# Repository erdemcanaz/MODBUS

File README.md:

# LoRa_Modbus
The goal of this project is to design a hardware implementation that enables wireless Modbus communication using the LoRa protocol.

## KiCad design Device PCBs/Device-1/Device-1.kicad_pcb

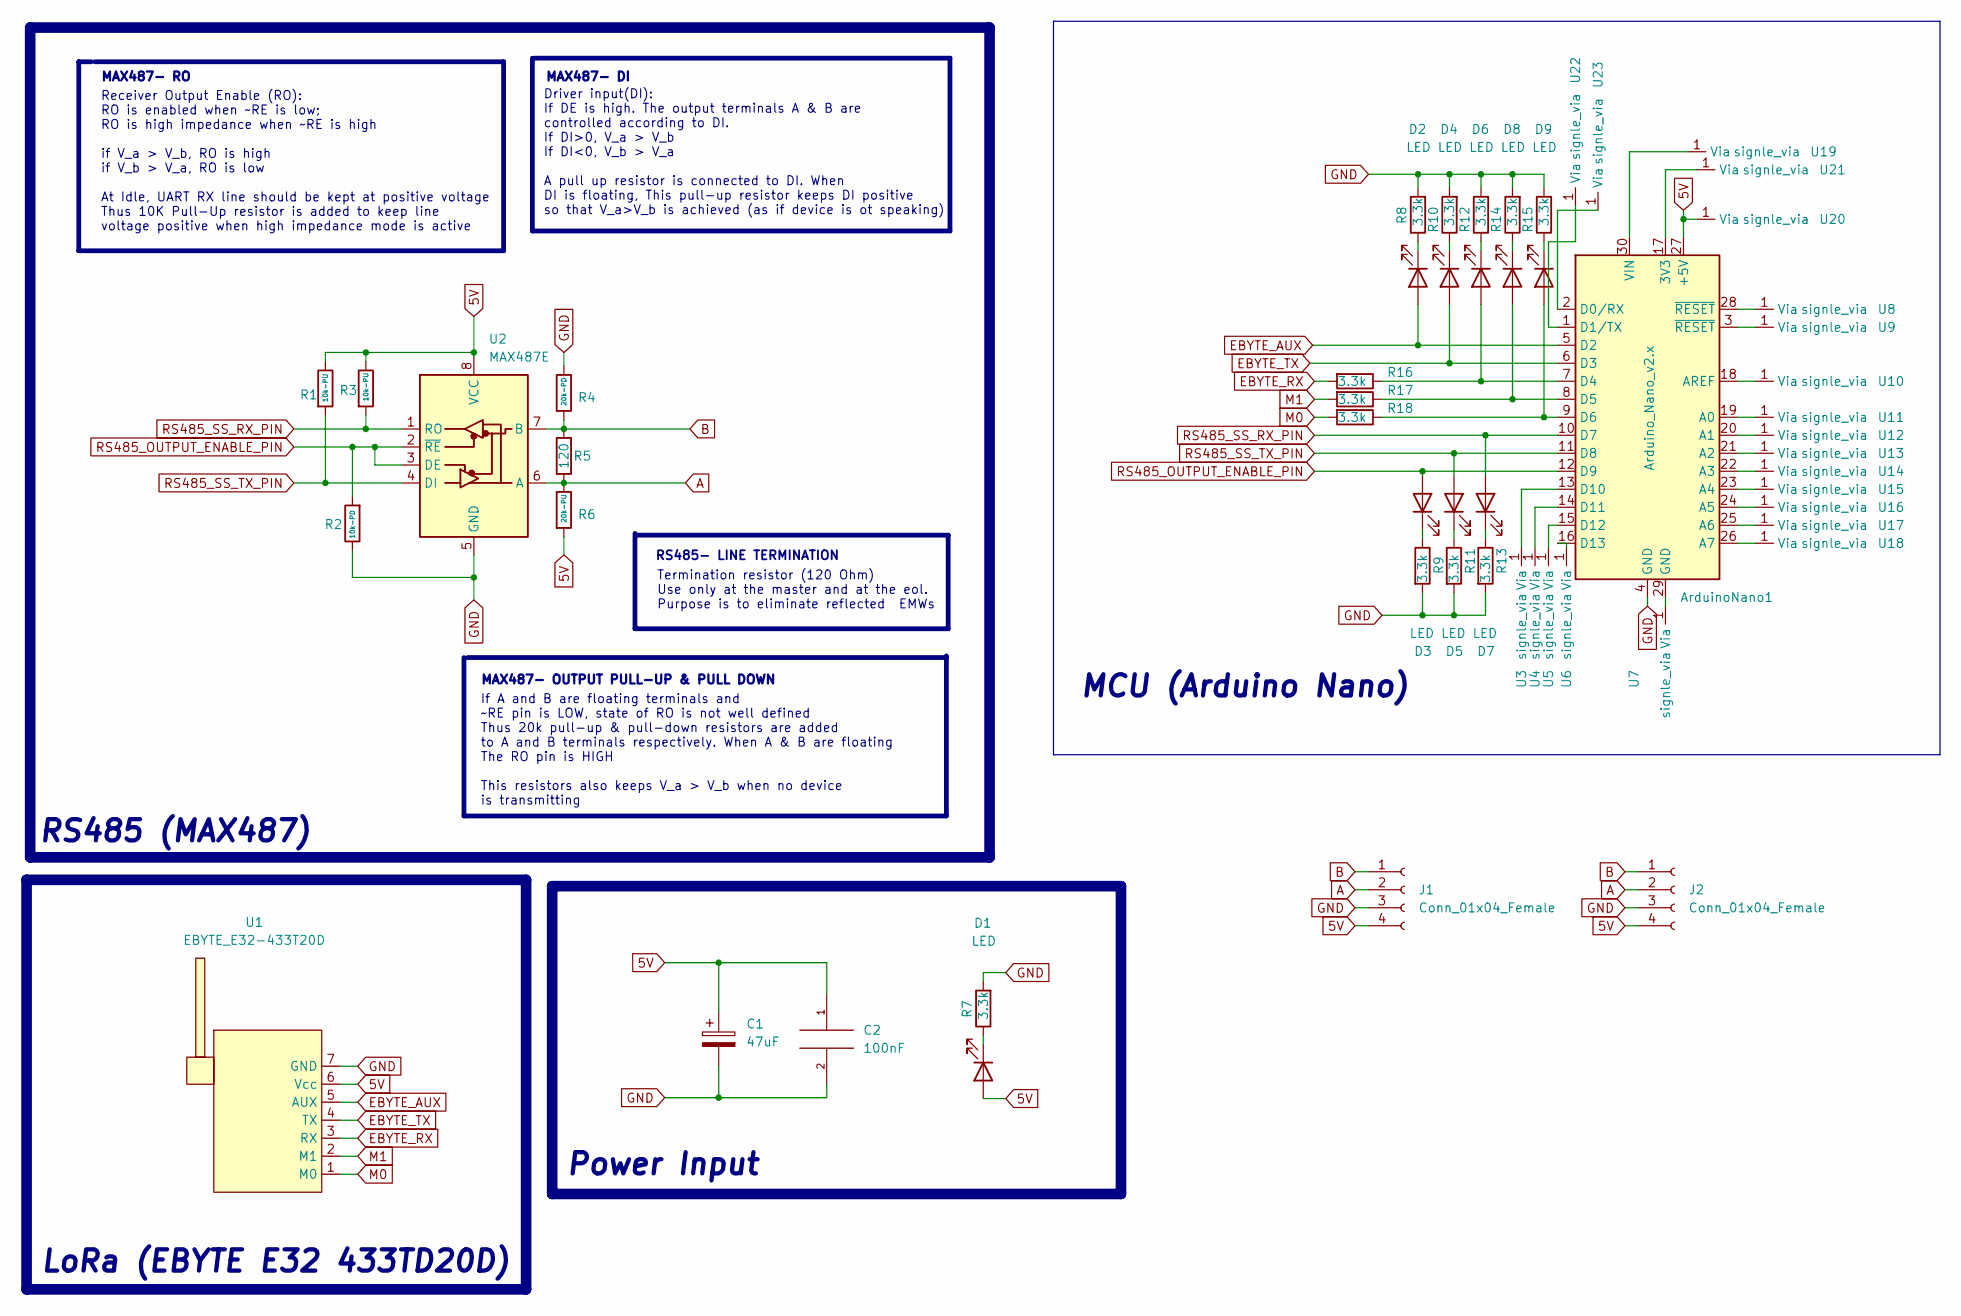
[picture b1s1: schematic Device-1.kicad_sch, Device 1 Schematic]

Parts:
ArduinoNano1: Arduino_Nano_v2.x; Arduino_Nano
C1: 47uF; CP_Elec_6.3x5.2
C2: 100nF; C_1206_3216Metric
D1, D2, D3, D8, D9: LED; lm281B-3000K
D4, D5, D6, D7: LED; lm281B-6500K
J1: Conn_01x04_Female; PinSocket_1x04_P2.54mm_Vertical
J2: Conn_01x04_Female; output_vias
R1, R3: 10k-PU; R_1206_3216Metric
R2: 10k-PD; R_1206_3216Metric
R4: 20k-PD; R_1206_3216Metric
R5: 120; R_1206_3216Metric
R6: 20k-PU; R_1206_3216Metric
R7, R8, R9, R10, R11, R12, R13, R14, R15, R16, R17, R18: 3.3k; R_1206_3216Metric
U1: EBYTE_E32-433T20D; EBYTE-E32-433T20D
U2: MAX487E; DIP-8_W7.62mm
U3, U4, U5, U6, U7, U8, U9, U10, U11, U12, U13, U14, U15, U16, U17, U18, U19, U20, U21, U22, U23: signle_via; single_via

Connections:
5V: ArduinoNano1.27 (+5V), C1.1, C2.1, D1.2 (A), J1.4, J2.4, R1.1, R3.1, R6.2, U1.6 (Vcc), U2.8 (VCC), U20.1 (Via)
A: J1.2, J2.2, R5.2, R6.1, U2.6 (A)
B: J1.1, J2.1, R4.2, R5.1, U2.7 (B)
EBYTE_AUX: ArduinoNano1.5 (D2), D2.2 (A), U1.5 (AUX)
EBYTE_RX: R16.2, U1.3 (RX)
EBYTE_TX: ArduinoNano1.6 (D3), D4.2 (A), U1.4 (TX)
GND: ArduinoNano1.4 (GND), C1.2, C2.2, J1.3, J2.3, R2.1, R4.1, R7.2, R8.2, R9.2, R10.2, R11.2, R12.2, R13.2, R14.2, R15.2, U1.7 (GND), U2.5 (GND)
M0: R18.2, U1.1 (M0)
M1: R17.2, U1.2 (M1)
unnamed: ArduinoNano1.1 (D1/TX), U22.1 (Via)
unnamed: ArduinoNano1.2 (D0/RX), U23.1 (Via)
unnamed: ArduinoNano1.3 (~RESET), U9.1 (Via)
unnamed: ArduinoNano1.7 (D4), D6.2 (A), R16.1
unnamed: ArduinoNano1.8 (D5), D8.2 (A), R17.1
unnamed: ArduinoNano1.9 (D6), D9.2 (A), R18.1
unnamed: ArduinoNano1.13 (D10), U3.1 (Via)
unnamed: ArduinoNano1.14 (D11), U4.1 (Via)
unnamed: ArduinoNano1.15 (D12), U5.1 (Via)
unnamed: ArduinoNano1.16 (D13), U6.1 (Via)
unnamed: ArduinoNano1.17 (3V3), U21.1 (Via)
unnamed: ArduinoNano1.18 (AREF), U10.1 (Via)
unnamed: ArduinoNano1.19 (A0), U11.1 (Via)
unnamed: ArduinoNano1.20 (A1), U12.1 (Via)
unnamed: ArduinoNano1.21 (A2), U13.1 (Via)
unnamed: ArduinoNano1.22 (A3), U14.1 (Via)
unnamed: ArduinoNano1.23 (A4), U15.1 (Via)
unnamed: ArduinoNano1.24 (A5), U16.1 (Via)
unnamed: ArduinoNano1.25 (A6), U17.1 (Via)
unnamed: ArduinoNano1.26 (A7), U18.1 (Via)
unnamed: ArduinoNano1.28 (~RESET), U8.1 (Via)
unnamed: ArduinoNano1.29 (GND), U7.1 (Via)
unnamed: ArduinoNano1.30 (VIN), U19.1 (Via)
unnamed: D1.1 (K), R7.1
unnamed: D2.1 (K), R8.1
unnamed: D3.1 (K), R9.1
unnamed: D4.1 (K), R10.1
unnamed: D5.1 (K), R11.1
unnamed: D6.1 (K), R12.1
unnamed: D7.1 (K), R13.1
unnamed: D8.1 (K), R14.1
unnamed: D9.1 (K), R15.1
RS485_OUTPUT_ENABLE_PIN: ArduinoNano1.12 (D9), D3.2 (A), R2.2, U2.2 (~RE), U2.3 (DE)
RS485_SS_RX_PIN: ArduinoNano1.10 (D7), D7.2 (A), R3.2, U2.1 (RO)
RS485_SS_TX_PIN: ArduinoNano1.11 (D8), D5.2 (A), R1.2, U2.4 (DI)

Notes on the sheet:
MAX487- OUTPUT PULL-UP & PULL DOWN
RS485- LINE TERMINATION
RS485 (MAX487)
Driver input(DI): If DE is high. The output terminals A & B are controlled according to DI. If DI>0, V_a > V_b If DI<0, V_b > V_a A pull up resistor is connected to DI. When DI is floating, This pull-up resistor keeps DI positive so that V_a>V_b is achieved (as if device is ot speaking)
If A and B are floating terminals and ~RE pin is LOW, state of RO is not well defined Thus 20k pull-up & pull-down resistors are added to A and B terminals respectively. When A & B are floating The RO pin is HIGH This resistors also keeps V_a > V_b when no device is transmitting
MAX487- RO
MAX487- DI
Power Input
Receiver Output Enable (RO): RO is enabled when ~RE is low; RO is high impedance when ~RE is high if V_a > V_b, RO is high if V_b > V_a, RO is low At Idle, UART RX line should be kept at positive voltage Thus 10K Pull-Up resistor is added to keep line voltage positive when high impedance mode is ac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
Termination resistor (120 Ohm) Use only at the master and at the eol. Purpose is to eliminate reflected EMWs
LoRa (EBYTE E32 433TD20D)
MCU (Arduino Nano)

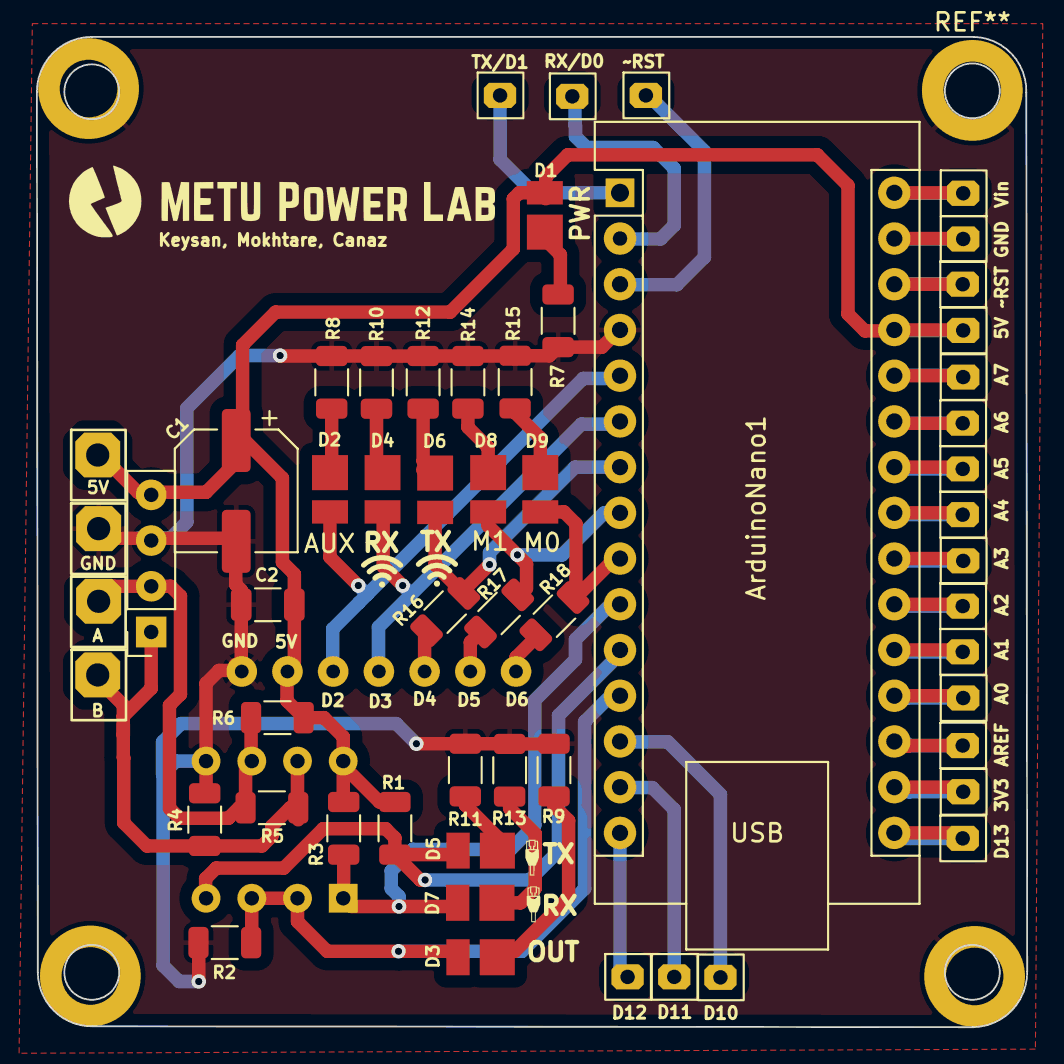
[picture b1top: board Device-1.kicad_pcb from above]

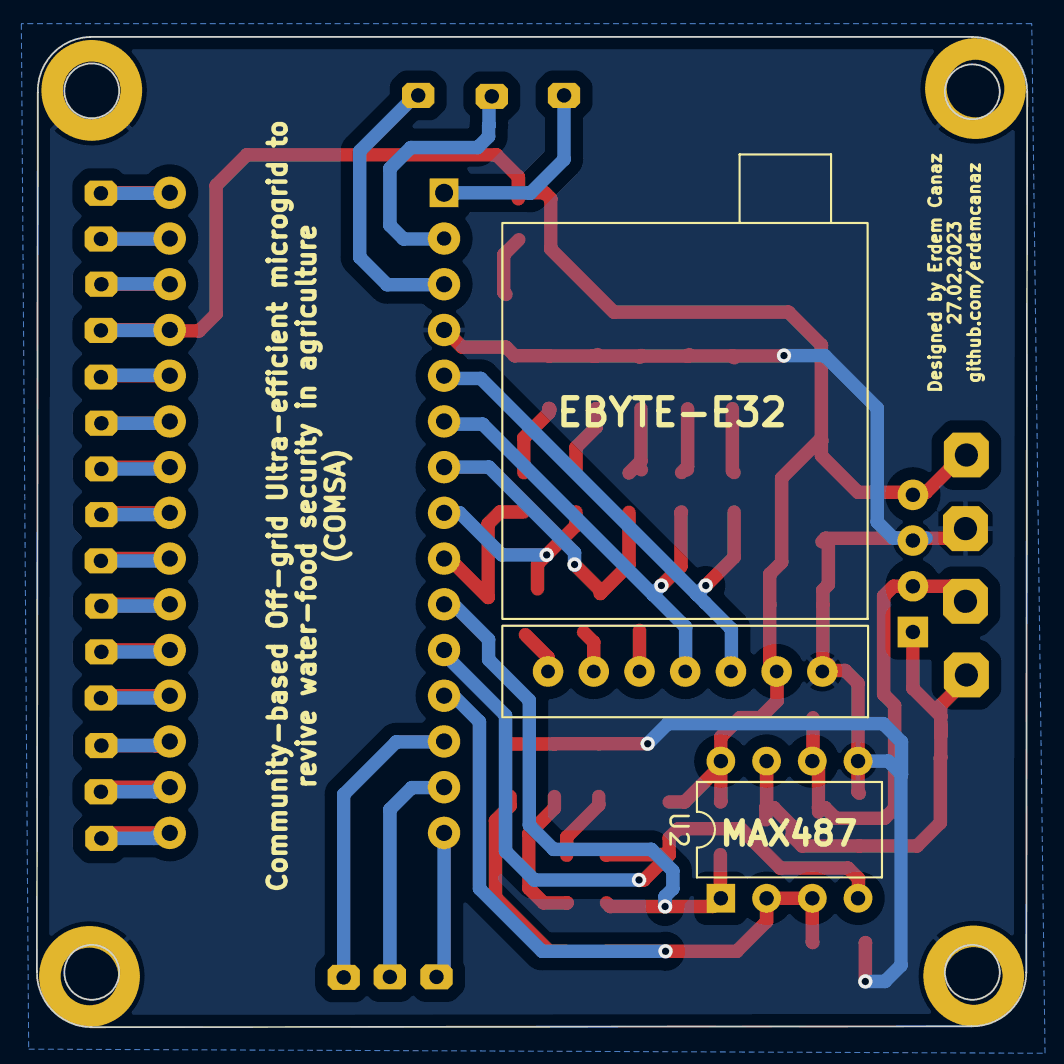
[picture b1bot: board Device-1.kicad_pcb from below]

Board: 2 copper layers, 55.0 x 55.0 mm, 55 parts (2 on the bottom side), 44 nets.

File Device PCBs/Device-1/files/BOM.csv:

Collated Components:,,,,,,,,,
Item,Qty,Reference(s),Value,Footprint,sipariþ adeti,,,,
1,1,ArduinoNano1,Arduino_Nano_v2.x,Module:Arduino_Nano,,,,,
2,1,C1,47uF,Capacitor_SMD:CP_Elec_6.3x5.2,12,,,,
3,1,C2,100nF,Capacitor_SMD:C_1206_3216Metric,20,,,,
4,5,"D1, D2, D3, D8, D9",LED,Device_1_project_footprints:lm281B-3000K,,,,,
5,4,"D4, D5, D6, D7",LED,Device_1_project_footprints:lm281B-6500K,,,,,
6,1,J1,Conn_01x04_Female,Connector_PinSocket_2.54mm:PinSocket_1x04_P2.54mm_Vertical,15,,,,
7,1,J2,Conn_01x04_Female,Device_1_project_footprints:output_vias,,,,,
8,2,"R1, R3",10k-PU,Resistor_SMD:R_1206_3216Metric,30,,,,
9,1,R2,10k-PD,Resistor_SMD:R_1206_3216Metric,15,,,,
10,1,R4,20k-PD,Resistor_SMD:R_1206_3216Metric,15,,,,
11,1,R5,120,Resistor_SMD:R_1206_3216Metric,30,,,,
12,1,R6,20k-PU,Resistor_SMD:R_1206_3216Metric,15,,,,
13,12,"R7, R8, R9, R10, R11, R12, R13, R14, R15, R16, R17, R18",3.3k,Resistor_SMD:R_1206_3216Metric,15,,,,
14,1,U1,EBYTE_E32-433T20D,Device_1_project_footprints:EBYTE-E32-433T20D,,,,,
15,1,U2,MAX487E,Package_DIP:DIP-8_W7.62mm,,,,,

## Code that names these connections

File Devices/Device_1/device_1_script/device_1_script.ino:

#include <SoftwareSerial.h>

//SOFTWARE RELATED STATIC VARIABLES
#define PACKAGE_SIZE_BYTE 44
#define HARDWARE_SERIAL_BAUD_RATE 9600
#define LORA_SOFTWARE_SERIAL_BAUD_RATE 9600
#define RS485_SOFTWARE_SERIAL_BAUD_RATE 9600

//HARDWARE RELATED STATIC VARIABLES
#define RS485_SOFTWARE_SERIAL_RX_PIN 7
#define RS485_SOFTWARE_SERIAL_TX_PIN 8
#define RS485_OUTPUT_ENABLE_PIN 9

#define EBYTE_M0_PIN 2
#define EBYTE_M1_PIN 3
#define EBYTE_TX_PIN 4  //Software serial RX
#define EBYTE_RX_PIN 5  //Software serial TX
#define EBYTE_AUX_PIN 6

#define DEVICE_CHANNEL 12  //0-255
#define DEVICE_ADDRESS 1 //0-65535
#define UART_PARITY_MODE 3 //3->8N1
#define UART_BAUD_MODE 3 //3-> 9600BPS
#define AIR_DATA_RATE_MODE 2 //2-> 2.4Kbps
#define FIXED_TRANSMISSION_MODE 1
#define IO_DRIVE_MODE 1 //1-> TX & AUX: push-pull, RX: pull-up
#define WIRELESS_WAKE_UP_MODE 0 //0-> 0.25kbps
#define FEC_MODE 1
#define POWER_MODE 0

//PARAMETRIC VARIABLES
#define DEBUG true
#define HARDWARE_SERIAL_WAIT_COMPUTER_TRANSFER_MS 10 
#define LORA_REQUEST_TIMEOUT_MS 750

//----------------------------------------------------------------------------
SoftwareSerial lora_serial_instance(EBYTE_TX_PIN, EBYTE_RX_PIN);  // software Rx, software Tx

void setup() {
  Serial.begin(HARDWARE_SERIAL_BAUD_RATE);
}

void loop() {
  listen_and_execute_valid_computer_orders();
}

uint16_t calculate_CRC(bool is_first_data, uint16_t previously_calculated_crc, uint16_t new_byte){ 
  uint16_t key = 40961; // 1010 0000 0000 0001
  if(is_first_data == true)previously_calculated_crc = 65535; //0xFFFF

  new_byte = new_byte ^ previously_calculated_crc;
  
  for (int i = 0; i < 8; i++)
  {
    bool should_XOR = false;
    if (new_byte % 2 == 1)
      should_XOR = true;
    new_byte = new_byte >> 1;
    if (should_XOR)
      new_byte = new_byte ^ key;
  }
  return new_byte;
}

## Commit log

2023-02-22 get_ebyte_parameters
    At this commit, the arduino is able to read the parameters of EBYTE-E32 series devices over software serial.
2023-02-22 device_1_master_is_finished
2023-02-22 set_ebyte_parameters
    In this commit, Arduino automatically overwrites the Ebyte E32 series device parameters. This is important because it allow us to use any device without preconfiguring. Just plug the lora device and 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
2023-02-24 Device 1 Slave and Master is finished
2023-02-24 Status code - Master is updated
2023-02-24 Status code - Slave is updated
2023-02-24 SerialMiddleware
2023-02-24 Python-Script SerialMiddleware is finished
2023-02-24 Python script is working well
2023-02-25 Arduino status codes
2023-02-25 Device-1 Schematic
2023-02-25 Device 1 PCB is finished
2023-02-27 slave config.h and tescom_SDDPV2200M
2023-03-01 PCB and slave fix
2023-03-01 PCBway gerbers are finished.
2023-03-10 Everything works
    1) PCB is finished (use larges holes for LoRa)
    2) Master and slave codes are finished
2023-03-24 Growat inverter is added as a device
2023-04-03 Machine labratory integration is started
2023-04-03 checkpoint
2023-04-05 main.py simplified
2023-04-05 Simple RS485 modbus slave is added
2023-04-05 Simple Slave- getter and setter
2023-04-07 water level modbus slave
2023-04-07 water level sensor driver
2023-04-07 First demo is done.
2023-04-07 First demo - end of the day
2023-04-11 Data logging
2023-04-12 12 hours of data measurement
2023-04-12 csv plotter
2023-04-12 device_tag is added
    knowing the device is important. But there are multiple of the same device. So I have added another column so called device_tag. This basically the human readable form of which device it is. Like, th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
2023-04-12 live script
2023-04-12 load power logger issue
2023-04-12 reliability test report is finished
2023-04-20 dummy slave
2023-04-23 3D lora
2023-05-01 DHT11-simple-modbus-slave
2023-05-01 firebase_test
2023-05-01 firebase-update block
2023-05-01 working continuous plot
2023-05-01 choosing which variables to plot
2023-05-01 firebase uı is finished
2023-05-09 Device Adress == LORA-ID
2023-06-12 late night fun
2023-06-25 set inverter charging current is added
2023-06-25 all sub functions to design algorithm is finished
2023-06-25 last commit of the night
2023-06-26 implementing algorithm
2023-06-27 run motor at desired frequency is finished
2023-06-27 Main algorithm is implemented
